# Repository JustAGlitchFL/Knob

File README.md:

# Knob
A multifunctional directional controller 

## Why?
This was inspired by both the BMW iDrive controller, and the Garmin G1000NXI avionics suite RANGE knob. The commonality between these two control interfaces is a multidirectional switch that has inputs for up, down, left, right, push, rotate ccw, and rotate cw. In the iDrive system, directional pushes move between radial menus, rotate moves between options in the menu, and push selects. This allows for intuitive control while keeping your attention focused on the road, rather than trying to poke touchscreen buttons. On the G1000NXI that I flew with at ERAU, the RANGE knob is used to zoom the map around your aircraft with rotation, panning the map, or clicking it to switch to cursor mode. In both of these situations, it has served an interesting role that no other input type could easily replace, and I thought it would be interesting to make it work on a computer.

## Assembly:
Just solder everything as shown in the KiCad Project, nothing special.

there is ***NO CASE*** for this project, as I am trying to keep this as small as I physically can (I also have no idea how much deflection there is on the switch and some other physical characteristics, so I wouldn't be able to a make a very good one as is)

## Pics

## BOM 
|Q  |Name             |Link                                                                                 |Price+ship                                   |Total |
|---|-----------------|-------------------------------------------------------------------------------------|---------------------------------------------|------|
|1  |Knob PCB         |                                                                                     |$8.22                                        |$30.96|
|1  |Alps RKJXT1F42001|https://www.digikey.com/en/products/detail/alps-alpine/RKJXT1F42001/19529127         |$22.74                                       |      |
|6  |SK6812MINI-E     |                                                                                     |on hand                                      |      |
|1  |XIAO RP2040      |https://www.digikey.com/en/products/detail/seeed-technology-co-ltd/102010428/14672129|included in the other to account for shipping|      |

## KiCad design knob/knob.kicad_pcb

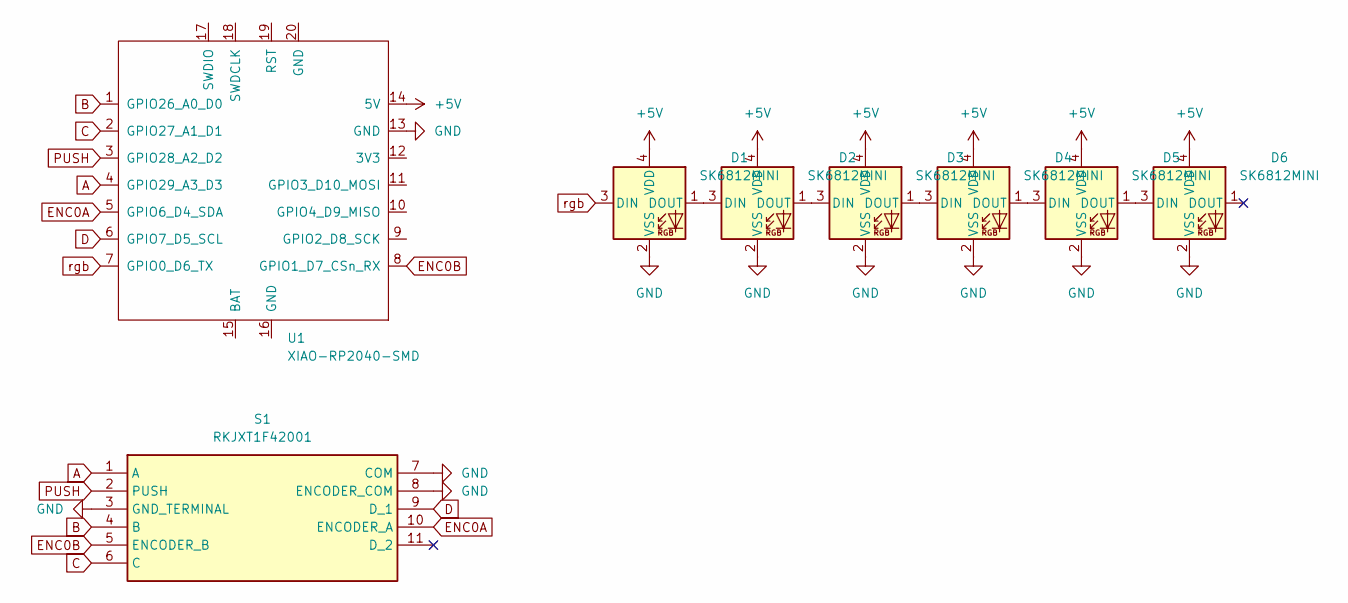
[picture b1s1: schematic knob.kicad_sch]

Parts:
D1, D2, D3, D4, D5, D6: SK6812MINI; SK6812MINI-E
S1: RKJXT1F42001; Manufacturer_Part_Number RKJXT1F42001; Mouser Part Number 688-RKJXT1F42001
U1: XIAO-RP2040-SMD

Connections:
+5V: D1.4 (VDD), D2.4 (VDD), D3.4 (VDD), D4.4 (VDD), D5.4 (VDD), D6.4 (VDD), U1.14 (5V)
A: S1.1 (A), U1.4 (GPIO29_A3_D3)
B: S1.4 (B), U1.1 (GPIO26_A0_D0)
C: S1.6 (C), U1.2 (GPIO27_A1_D1)
D: S1.9 (D_1), U1.6 (GPIO7_D5_SCL)
ENC0A: S1.10 (ENCODER_A), U1.5 (GPIO6_D4_SDA)
ENC0B: S1.5 (ENCODER_B), U1.8 (GPIO1_D7_CSn_RX)
GND: D1.2 (VSS), D2.2 (VSS), D3.2 (VSS), D4.2 (VSS), D5.2 (VSS), D6.2 (VSS), S1.3 (GND_TERMINAL), S1.7 (COM), S1.8 (ENCODER_COM), U1.13 (GND)
unnamed: D1.1 (DOUT), D2.3 (DIN)
unnamed: D2.1 (DOUT), D3.3 (DIN)
unnamed: D3.1 (DOUT), D4.3 (DIN)
unnamed: D4.1 (DOUT), D5.3 (DIN)
unnamed: D5.1 (DOUT), D6.3 (DIN)
PUSH: S1.2 (PUSH), U1.3 (GPIO28_A2_D2)
rgb: D1.3 (DIN), U1.7 (GPIO0_D6_TX)

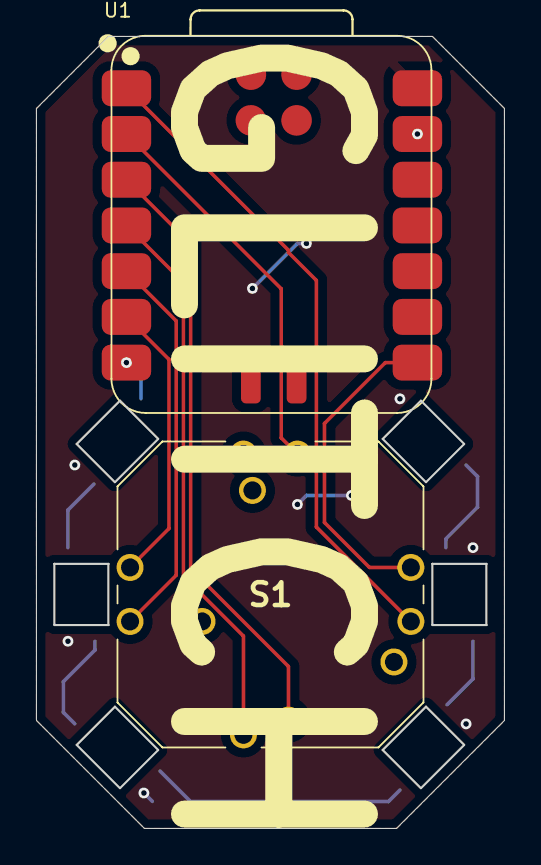
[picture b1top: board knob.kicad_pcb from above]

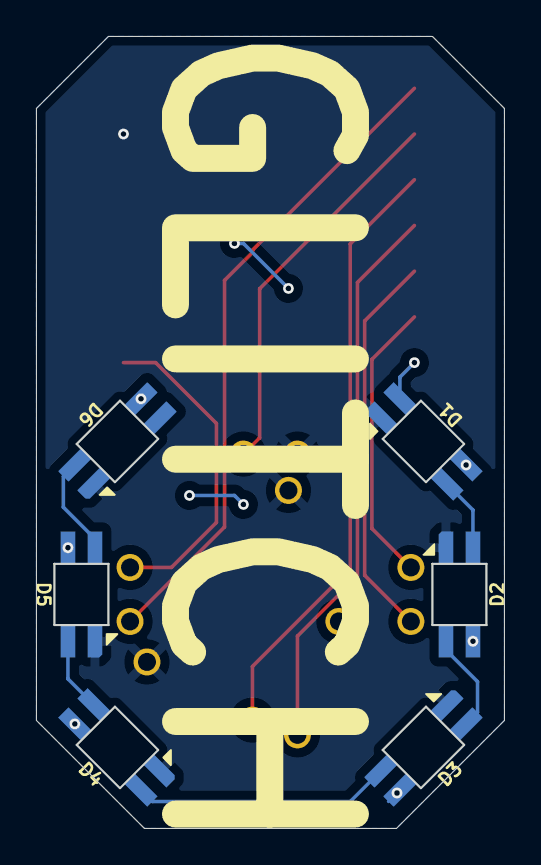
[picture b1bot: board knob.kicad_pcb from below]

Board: 2 copper layers, 25.9 x 43.9 mm, 8 parts (6 on the bottom side), 15 nets.

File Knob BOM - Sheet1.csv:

Q,Name,Link,Price+ship,Total
1,Knob PCB,,$8.22,$30.96
1,Alps RKJXT1F42001,https://www.digikey.com/en/products/detail/alps-alpine/RKJXT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,$22.74,
6,SK6812MINI-E,,on hand,
1,XIAO RP2040,https://www.digikey.com/en/products/detail/seeed-technology-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,included in the other to account for shipping,

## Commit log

2025-06-12 intial
2025-06-13 sync
2025-06-19 bom table
2025-06-20 move csv
2025-07-08 images
2025-07-31 image
2025-07-31 push
2025-08-06 Specificity on design decisions
2025-08-06 add fw
